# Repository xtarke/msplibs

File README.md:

# MSP430 libs: exemplos para Microcontroladores MSP430

Notas, exemplos e bibliotecas para a disciplina de Microntroladores do Instituto Ferderal de Santa Catarina

## Getting Started

Clone o repositório e adicione os arquivos no seu projeto. Evite compilar mais de uma função main.

## Circuitos

- [Hardware LCD e IRQ externo](./figuras/display_irq.png)
- [Hardware diplays de 7 segmentos e WDT](./figuras/wdt_disp.png)

## Gravação com MSPDEBUG

```bash
mspdebug -n rf2500 "prog ./Debug/msplibs.out"
```

[Launchpad Linux](https://hackaday.com/2010/08/11/how-to-launchpad-programming-with-linux/)

https://dlbeer.co.nz/mspdebug/

##  Launchpad G2553

	- Inverter os jumpers Rx e TX no kit para receber/enviar comandos pela UART e computador.

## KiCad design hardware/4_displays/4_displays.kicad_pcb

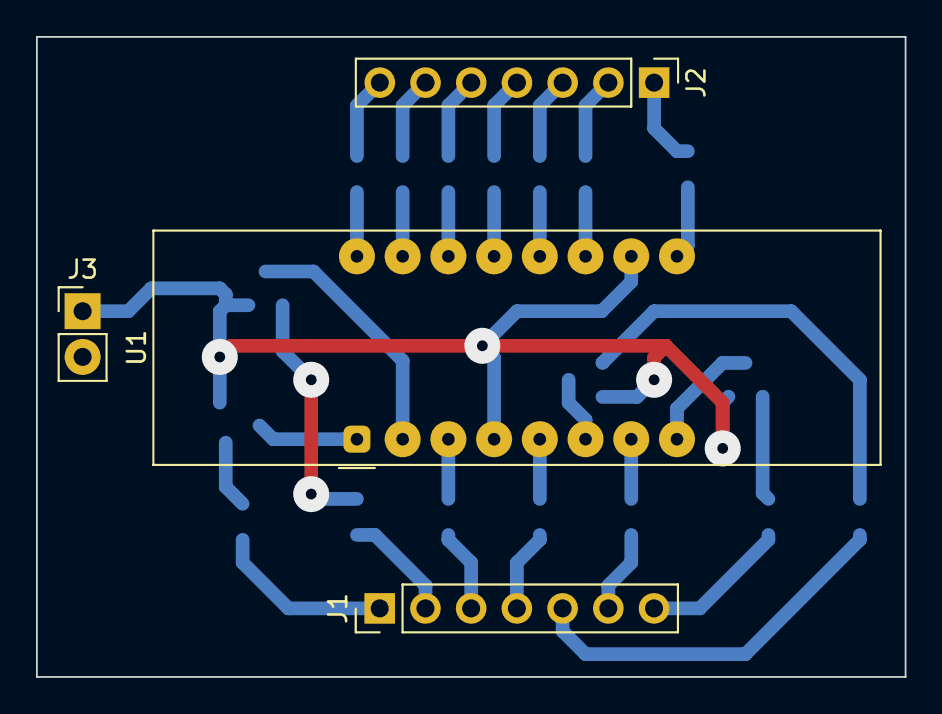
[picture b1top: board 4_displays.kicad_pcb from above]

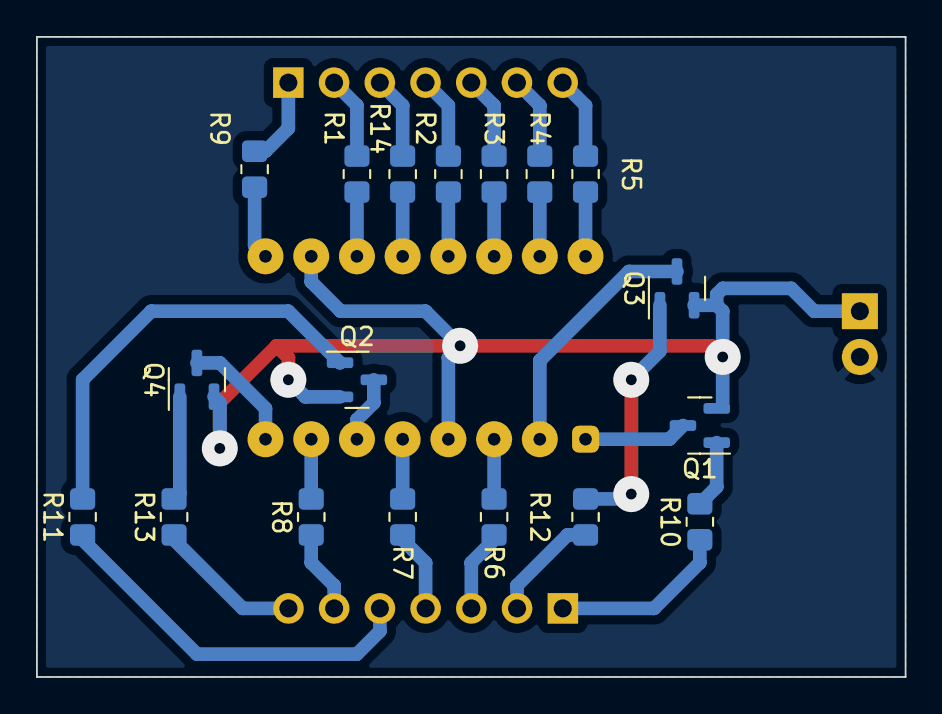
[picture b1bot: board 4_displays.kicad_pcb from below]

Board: 2 copper layers, 48.3 x 35.6 mm, 22 parts (18 on the bottom side), 33 nets.

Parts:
J1, J2: Conn_01x07_Male; PinHeader_1x07_P2.54mm_Vertical
J3: Conn_01x02_Male; PinHeader_1x02_P2.54mm_Vertical
Q1, Q2, Q3, Q4: BC807; SOT-23
R1, R2, R3, R4, R5, R6, R7, R8, R9, R14: 330; R_0805_2012Metric_Pad1.20x1.40mm_HandSolder
R10, R11, R12, R13: 2k2; R_0805_2012Metric_Pad1.20x1.40mm_HandSolder
U1: LTC-4627JG; LTC-4627Jx

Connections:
+3V3: J3.1, Q1.2 (E), Q2.2 (E), Q3.2 (E), Q4.2 (E), U1.4 (AL1-2), U1.10 (AL3)
A: R3.1, U1.14 (A)
B: R5.1, U1.16 (B)
C: R2.2, U1.13 (C)
CA1: Q1.3 (C), U1.1 (CA1)
CA2: Q3.3 (C), U1.2 (CA2)
CA3: Q2.3 (C), U1.6 (CA3)
CA4: Q4.3 (C), U1.8 (CA4)
CL1-2: R14.2, U1.12 (CL1-2)
CL3: R9.2, U1.9 (CL3)
D: R6.2, U1.3 (D)
D1: J1.1, R10.1
D2: J1.2, R12.1
D3: J1.5, R11.1
D4: J1.7, R13.1
DP: R8.2, U1.7 (DP)
E: R7.2, U1.5 (E)
F: R1.2, U1.11 (F)
G: R4.2, U1.15 (G)
unnamed: Q1.1 (B), R10.2
unnamed: Q2.1 (B), R11.2
unnamed: Q3.1 (B), R12.2
unnamed: Q4.1 (B), R13.2
unnamed: J2.2, R1.1
unnamed: J2.4, R2.1
unnamed: J2.5, R3.2
unnamed: J2.6, R4.1
unnamed: J2.7, R5.2
unnamed: J1.3, R6.1
unnamed: J1.4, R7.1
unnamed: J1.6, R8.1
unnamed: J2.1, R9.1
unnamed: J2.3, R14.1

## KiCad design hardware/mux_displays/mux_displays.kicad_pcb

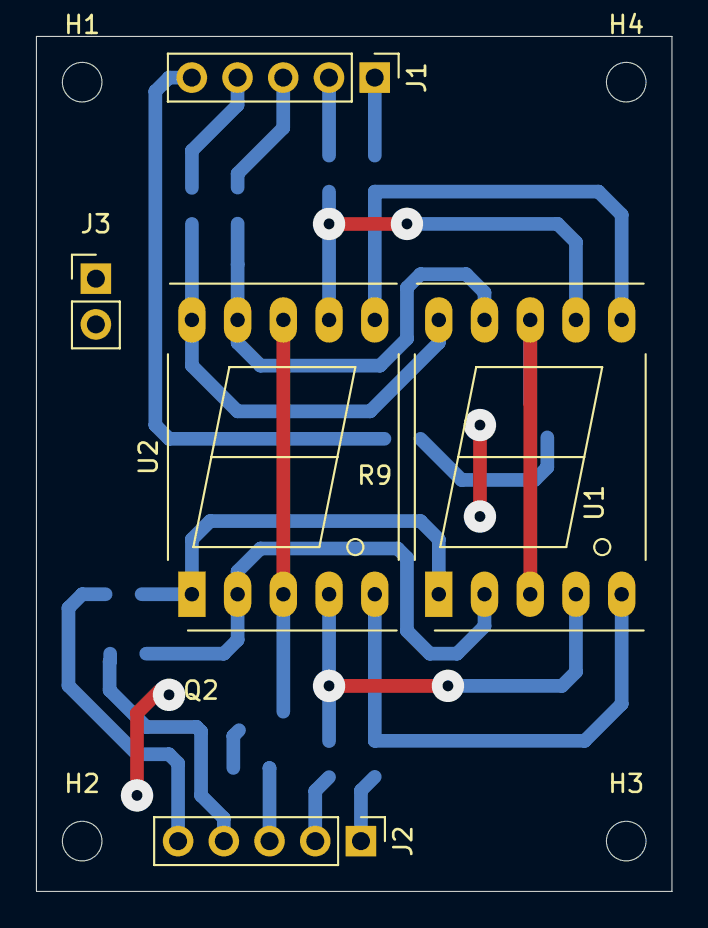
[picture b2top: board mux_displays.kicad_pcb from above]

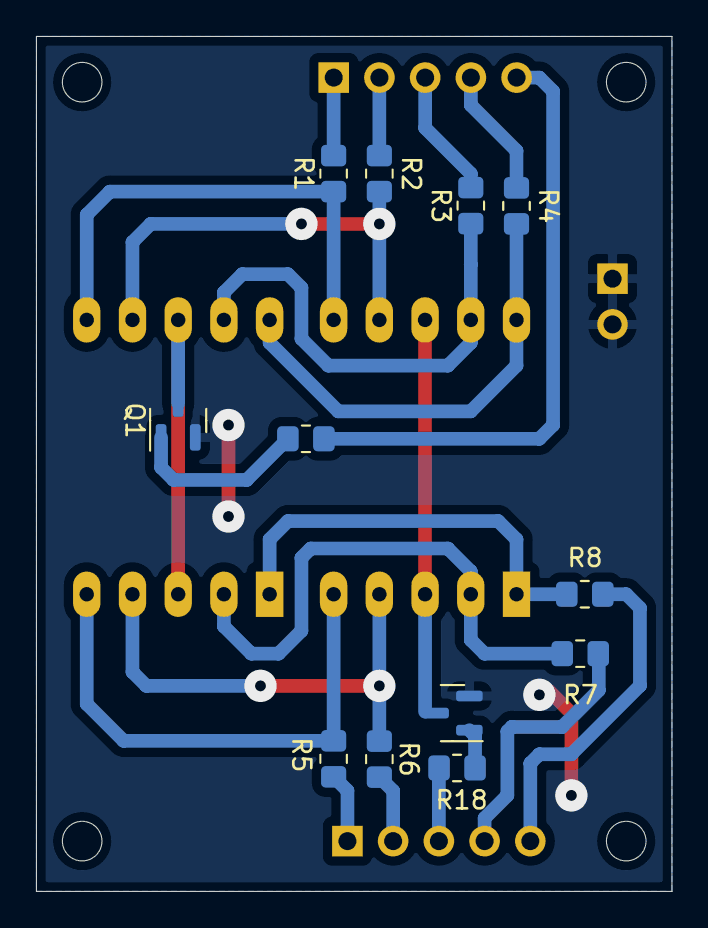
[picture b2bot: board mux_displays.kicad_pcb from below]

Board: 2 copper layers, 35.3 x 47.5 mm, 21 parts (12 on the bottom side), 23 nets.

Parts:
H1, H2, H3, H4: MountingHole; MountingHole_2.2mm_M2
J1, J2: Conn_01x05_Male; PinHeader_1x05_P2.54mm_Vertical
J3: Conn_01x02_Male; PinHeader_1x02_P2.54mm_Vertical
Q1, Q2: BC817; SOT-23
R1, R2, R3, R4, R5, R6, R7, R8: 330; R_0805_2012Metric_Pad1.20x1.40mm_HandSolder
R9, R18: 2k2; R_0805_2012Metric_Pad1.20x1.40mm_HandSolder
U1, U2: KCSC02-123; 7SegmentLED_LTS6760_LTS6780

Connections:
A: R2.1, U1.7 (A), U2.7 (A)
B: R1.1, U1.6 (B), U2.6 (B)
C: R6.1, U1.4 (C), U2.4 (C)
D: R7.1, U1.2 (D), U2.2 (D)
D1: J1.5, R9.2
D2: J2.3, R18.2
DP: R5.1, U1.5 (DP), U2.5 (DP)
E: R8.1, U1.1 (E), U2.1 (E)
F: R3.1, U1.9 (F), U2.9 (F)
G: R4.1, U1.10 (G), U2.10 (G)
GND: J3.1, J3.2, Q1.2 (E), Q2.2 (E)
unnamed: J1.1, R1.2
unnamed: J1.2, R2.2
unnamed: J1.3, R3.2
unnamed: J1.4, R4.2
unnamed: J2.1, R5.2
unnamed: J2.2, R6.2
unnamed: J2.4, R7.2
unnamed: J2.5, R8.2
unnamed: Q1.1 (B), R9.1
unnamed: Q1.3 (C), U1.3 (CC), U1.8 (CC)
unnamed: Q2.1 (B), R18.1
unnamed: Q2.3 (C), U2.3 (CC), U2.8 (CC)

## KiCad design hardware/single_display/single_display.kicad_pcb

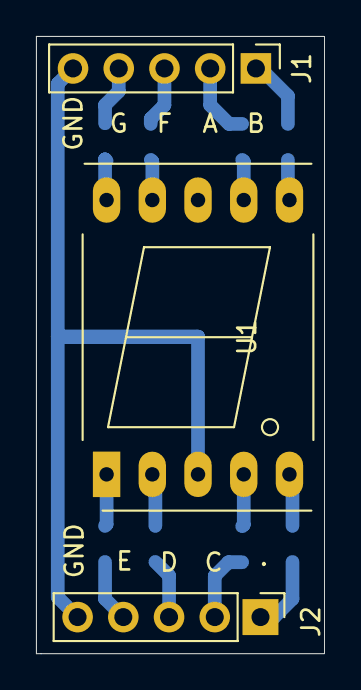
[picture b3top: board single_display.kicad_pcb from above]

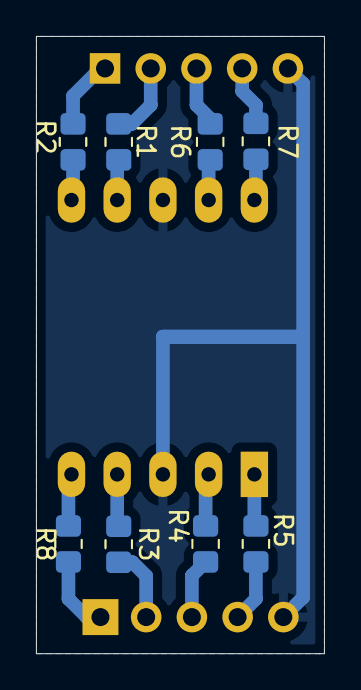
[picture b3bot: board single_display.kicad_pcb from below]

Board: 2 copper layers, 16.0 x 34.3 mm, 11 parts (8 on the bottom side), 17 nets.

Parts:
J1, J2: Conn_01x05_Male; PinHeader_1x05_P2.54mm_Vertical
R1, R2, R3, R4, R5, R6, R7, R8: 330; R_0805_2012Metric_Pad1.20x1.40mm_HandSolder
U1: KCSC02-123; 7SegmentLED_LTS6760_LTS6780

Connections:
A: J1.2, R1.2
B: J1.1, R2.2
C: J2.2, R3.2
D: J2.3, R4.2
DP: J2.1, R8.2
E: J2.4, R5.2
F: J1.3, R6.2
G: J1.4, R7.2
GND: J1.5, J2.5, U1.3, U1.8
unnamed: R1.1, U1.7
unnamed: R2.1, U1.6
unnamed: R3.1, U1.4
unnamed: R4.1, U1.2
unnamed: R5.1, U1.1
unnamed: R6.1, U1.9
unnamed: R7.1, U1.10
unnamed: R8.1, U1.5

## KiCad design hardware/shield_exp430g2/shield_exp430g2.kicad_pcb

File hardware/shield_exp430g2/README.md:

# Interface shield

This shield connects all microcontroller (MSP-EXP430G2 - MSP430G2553) pins to the car's power board. Go to [Power Board](https://github.com/xtarke/avrlibs/tree/master/shields/carrinho_potencia) for more hardware information.

See [this schematic](schematic.pdf).

## Analog pins

| Analog input  | MSP pin  | Board label  | Signal |
| ------------- | -------- | ------------ | ------ |
| A0            | P1.0     |   ADC0       | Bat0   |
| A3            | P1.3     |   ADC1       | Bat1   |
| ?             |  ?       |   ADC2       | Ampop1 |
| ?             |  ?       |   ADC3       | Ampop2 |

## Ultrasonic sensor

| MSP Pin | Signal|
| ------- | ------|
| P1.5    | Echo0 |
| P1.4    | Trig0 |
| P1.6    | Echo1 |
| P1.7    | Trig1 |

## Motors

**Caution**, P2.1 and P2.2 are connected to the same timer comparator as well as P2.4 and P2.5.

| MSP Pin    | Signal|  Board label |
| ---------- | ------| ------------ |
| P2.1/TA1.1 | PWM1  |  M1          |
| P2.2/TA1.1 | PWM1N |  M1N         |
| P2.4/TA1.2 | PWM2  |  M2          |
| P2.5/TA1.2 | PWM2N |  M2N         |

## Espeed econder

| MSP Pin | Signal |  Board label |
| ------- | ------ | ------------ |
| P2.6    | D0     | ENC0         |
| P2.7    | D1     | ENC1         |

## Optic sensor

| MSP Pin | Signal | Board label |
| ------- | ------ | ----------- |
| P2.0    | R_TCRT | R DIR       |
| P2.3    | L_TCRT | L ESQ       |

## UART

| MSP Pin | Signal |
| ------- | ------ |
| P1.2    | TX     |
| P1.3    | RX     |

## Assembly

EXP430G2 with MSP430G2553 
Shield and EXP430G2 
Power board. Connection with 26 pin flat cable

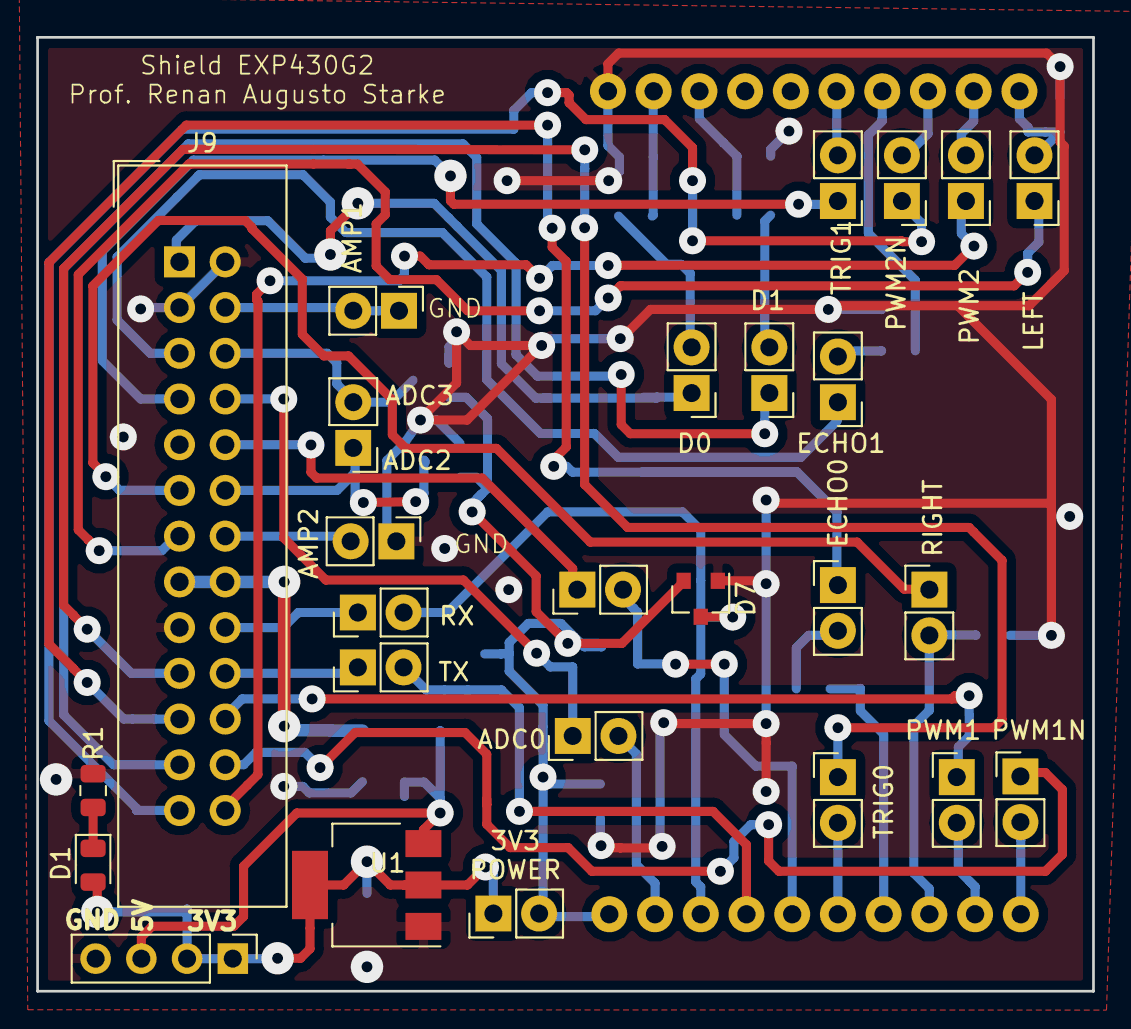
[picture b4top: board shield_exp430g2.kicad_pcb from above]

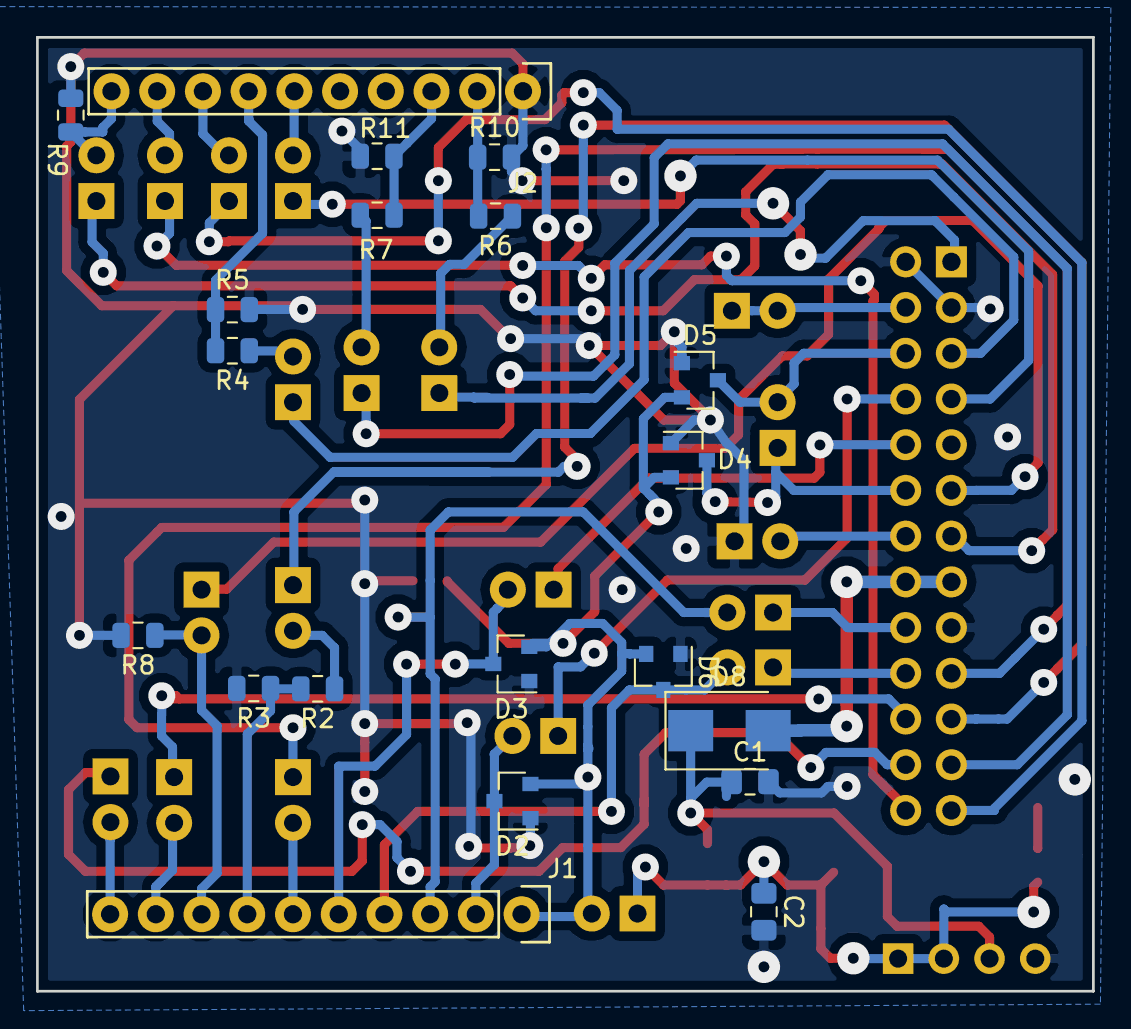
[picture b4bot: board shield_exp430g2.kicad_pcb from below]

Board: 2 copper layers, 58.7 x 53.0 mm, 46 parts (20 on the bottom side), 46 nets.

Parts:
C1, C2: 100n; C_0805_2012Metric_Pad1.15x1.40mm_HandSolder
D1: LED; LED_0805_2012Metric
D2, D3, D4, D5, D6, D7: BAT54S; SOT-23
D8: D_Schottky; D_SMB
J1, J2: Digital; Socket_Strip_Arduino_1x10
J3, J4, J5, J6, J7, J8, J10, J11, J12, J13, J15, J16, J17, J18, J19, J20, J21, J22, J23, J24: Conn_01x02_Male; PinHeader_1x02_P2.54mm_Vertical
J9: Conn_02x13_Odd_Even; IDC-Header_2x13_P2.54mm_Vertical
J14: Conn_01x04_Male; PinHeader_1x04_P2.54mm_Vertical
R1: R; R_0805_2012Metric
R2, R4, R6, R7: 10k; R_0805_2012Metric
R3, R5, R8, R9, R10, R11: 15k; R_0805_2012Metric
U1: NCP1117-3.3_SOT223; SOT-223-3_TabPin2

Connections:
+3V3: D2.2, D3.2, D4.2, D5.2, D6.2, D7.2, J1.1, J3.2
+5V: C1.1, D8.1, J14.3, U1.3
+5VP: D8.2, J9.15, J9.16
ADC0: J6.1, J9.8
ADC1: J7.1, J9.10
ADC2: D4.3, J8.1, J9.12
ADC3: D5.3, J8.2, J9.6
AMP1: J4.1, J4.2, J9.4
AMP2: J5.2, J9.14
D0: J9.1, J21.1
D1: J9.23, J24.1
Echo0: J9.21, J10.1
Echo1: J9.5, J12.1
GND: C1.2, C2.2, D2.1, D3.1, D4.1, D5.1, D6.1, D7.1, J2.1, J5.1, J9.2, J9.3, J9.17, J14.4, R1.2, R3.2, R5.2, R8.2, R9.2, R10.2, R11.2, U1.1
L_TCRT: J9.13, J20.1
unnamed: C2.1, D1.2, J3.1, J14.1, J14.2, U1.2
unnamed: D1.1, R1.1
unnamed: J10.2, R2.1
unnamed: J12.2, R4.1
unnamed: J21.2, R6.1
unnamed: J24.2, R7.1
P1.0: D2.3, J1.2, J6.2
P1.1: D7.3, J1.3, J23.2
P1.2: D6.3, J1.4, J22.2
P1.3: D3.3, J1.5, J7.2
P1.4: J1.6, J11.2
P1.5: J1.7, R2.2, R3.1
P1.6: J2.7, R4.2, R5.1
P1.7: J2.6, J13.2
P2.0: J1.8, J19.2, R8.1
P2.1: J1.9, J15.2
P2.2: J1.10, J16.2
P2.3: J2.10, J20.2, R9.1
P2.4: J2.9, J17.2
P2.5: J2.8, J18.2
P2.6: J2.2, R6.2, R10.1
P2.7: J2.3, R7.2, R11.1
PWM1: J9.22, J15.1
PWM1N: J9.24, J16.1
PWM2: J9.26, J17.1
PWM2N: J9.25, J18.1
RXB: J9.20, J22.1
R_TCRT: J9.11, J19.1
TXB: J9.18, J23.1
Trig0: J9.19, J11.1
Trig1: J9.7, J13.1

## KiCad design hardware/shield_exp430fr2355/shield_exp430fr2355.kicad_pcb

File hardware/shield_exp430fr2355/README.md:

# Interface shield

This shield connects microcontroller (MSP-EXP430FR2355) pins to the car's power board. Go to [Power Board](https://github.com/xtarke/avrlibs/tree/master/shields/carrinho_potencia) for more hardware information.

See [this schematic](schematic.pdf).

## Analog pins

| Analog input  | MSP pin  | Board label  | Signal |
| ------------- | -------- | ------------ | ------ |
| A1            | P1.1     |   ADC0       | Bat0   |
| A2            | P1.2     |   ADC1       | Bat1   |
| ?             |  ?       |   ADC2       | Ampop1 |
| ?             |  ?       |   ADC3       | Ampop2 |

## Ultrasonic sensor

| MSP Pin | Signal|
| ----------- | ------|
| P2.0/TB1.1  | Echo0 |
| P2.2        | Trig0 |
| P2.1/TB1.2  | Echo1 |
| P2.4        | Trig1 |

## Motors

| MSP Pin    | Signal|  Board label |
| ---------- | ------| ------------ |
| P6.0/TB3.1 | PWM1  |  M1          |
| P6.1/TB3.2 | PWM1N |  M1N         |
| P6.2/TB3.3 | PWM2  |  M2          |
| P6.3/TB3.4 | PWM2N |  M2N         |

## Espeed econder

| MSP Pin | Signal |  Board label |
| ------- | ------ | ------------ |
| P5.0    | D0     | ENC0         |
| P5.1    | D1     | ENC1         |

## Optic sensor

| MSP Pin | Signal | Board label |
| ------- | ------ | ----------- |
| P5.4    | R_TCRT | R DIR       |
| P3.0    | L_TCRT | L ESQ       |

## UART

| MSP Pin | Signal |
| ------- | ------ |
| P1.7    | TX     |
| P1.6    | RX     |

## Assembly

Shield and EXP430FR2355 

Shield, EXP430FR2355 and chassi. 

Power board. Connection with 26 pin flat cable

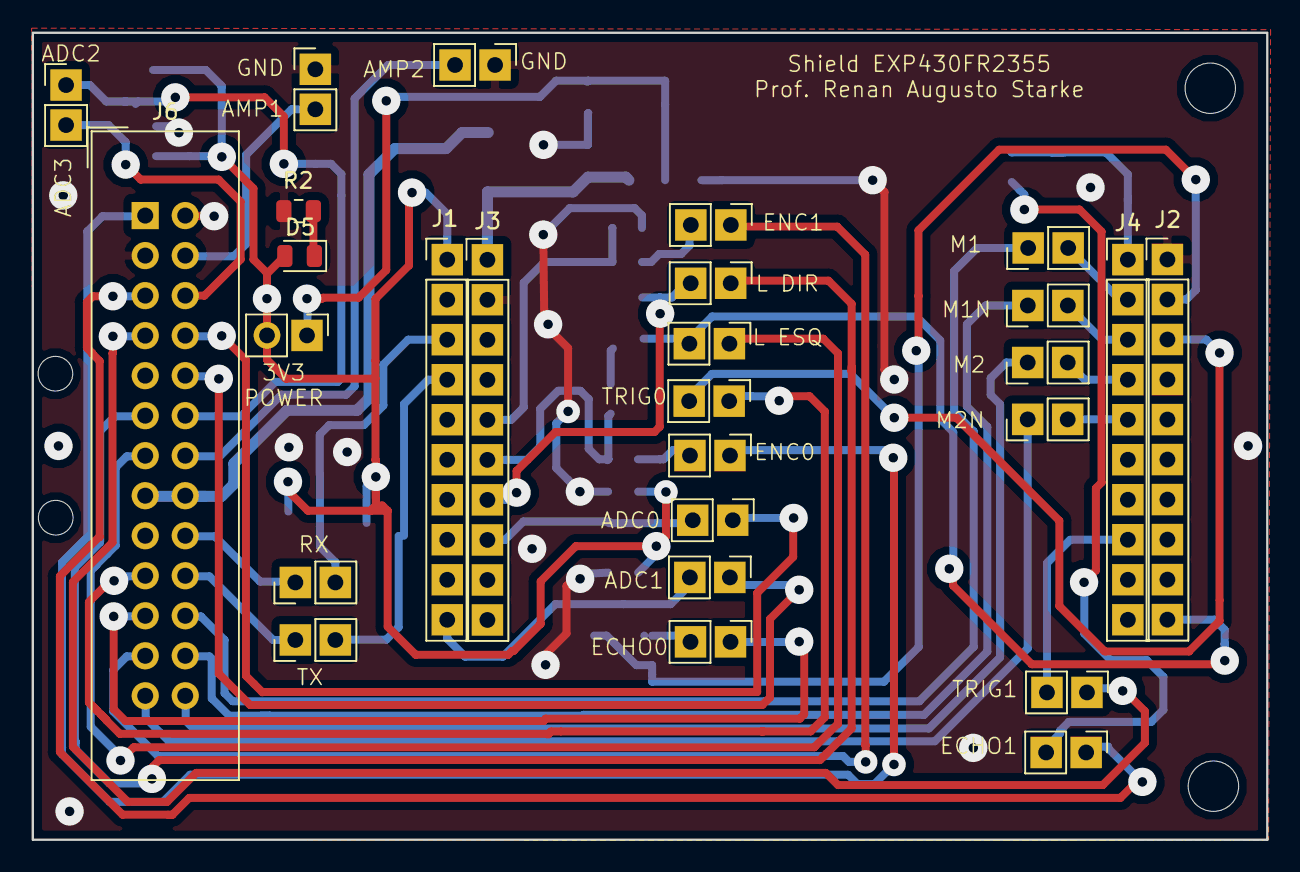
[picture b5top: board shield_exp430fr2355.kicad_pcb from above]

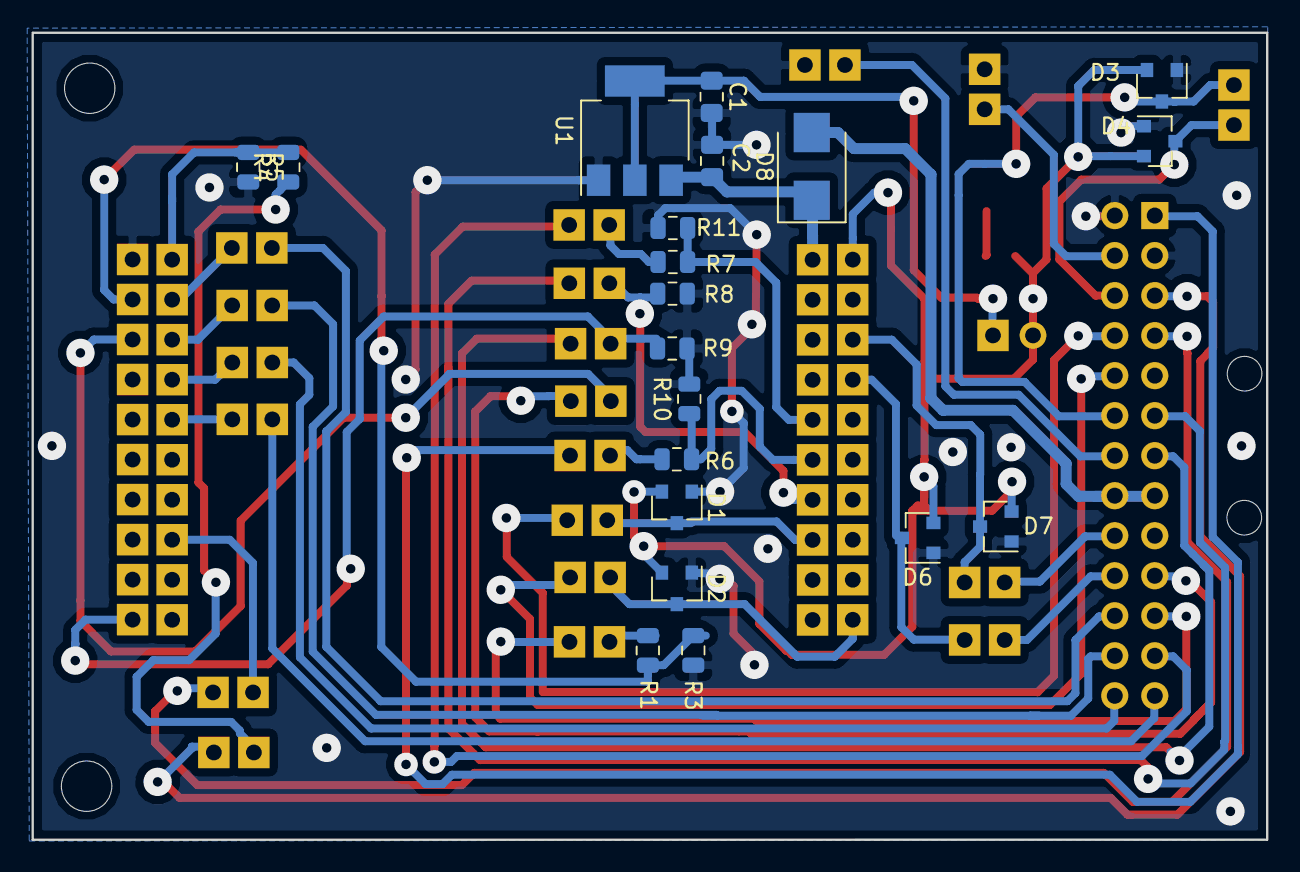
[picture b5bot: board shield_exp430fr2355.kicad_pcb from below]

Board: 2 copper layers, 78.4 x 51.2 mm, 51 parts (20 on the bottom side), 46 nets.

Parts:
C1, C2: 100n; C_0805_2012Metric_Pad1.15x1.40mm_HandSolder
D1, D2, D3, D4, D6, D7: BAT54S; SOT-23
D5: LED; LED_0805_2012Metric
D8: D_Schottky; D_SMB
H1, H2: MountingHole; MountingHole_2.2mm_M2
H3, H4: MountingHole; MountingHole_3.2mm_M3
J1: TI_BOOSTER_40_J1; PinHeader_1x10_P2.54mm_Vertical
J2: TI_BOOSTER_40_J2; PinHeader_1x10_P2.54mm_Vertical
J3: TI_BOOSTER_40_J3; PinHeader_1x10_P2.54mm_Vertical
J4: TI_BOOSTER_40_J4; PinHeader_1x10_P2.54mm_Vertical
J6: Conn_02x13_Odd_Even; IDC-Header_2x13_P2.54mm_Vertical
J7, J8, J9, J10, J12, J13, J14, J15, J16, J17, J18, J19, J20, J21, J22, J23, J24, J25, J27, J28: Conn_01x02_Male; PinHeader_1x02_P2.54mm_Vertical
R1, R4, R6, R7: 10k; R_0805_2012Metric
R2: 820R; R_0805_2012Metric
R3, R5, R10, R11: 15k; R_0805_2012Metric
R8, R9: 15K; R_0805_2012Metric
U1: NCP1117-3.3_SOT223; SOT-223-3_TabPin2

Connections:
+3V3: D1.2, D2.2, D3.2, D4.2, D5.2, D6.2, D7.2, J1.1, J7.2
+5V: C2.1, D8.1, J3.1, U1.3
+5VP: D8.2, J6.15, J6.16
ADC0: J6.8, J12.1
ADC1: J6.10, J21.1
ADC2: D3.3, J6.12, J8.1
ADC3: D4.3, J6.6, J8.2
AMP1: J6.4, J9.2
AMP2: J6.14, J10.2
D0: J6.1, J22.1
D1: J6.23, J23.1
Echo0: J6.21, J13.1
Echo1: J6.5, J19.1
GND: C1.2, C2.2, D1.1, D2.1, D3.1, D4.1, D6.1, D7.1, J2.1, J3.2, J6.2, J6.3, J9.1, J10.1, R2.2, R3.2, R5.2, R8.2, R9.2, R10.2, R11.2, U1.1
L_TCRT: J6.13, J25.1
unnamed: C1.1, J7.1, U1.2
unnamed: D5.1, R2.1
unnamed: J13.2, R1.1
unnamed: J19.2, R4.1
unnamed: J22.2, R6.1
unnamed: J23.2, R7.1
P1.1: D1.3, J3.8, J12.2
P1.2: D2.3, J1.10, J21.2
P1.6: D7.3, J1.3, J28.2
P1.7: D6.3, J1.4, J27.2
P2.0: J2.2, R1.2, R3.1
P2.1: J4.1, R4.2, R5.1
P2.2: J2.3, J14.2
P2.4: J4.8, J20.2
P3.0: J2.10, J25.2, R9.1
P5.0: J3.6, R6.2, R10.1
P5.1: J3.5, R7.2, R11.1
P5.4: J3.7, J24.2, R8.1
P6.0: J4.2, J15.2
P6.1: J4.3, J16.2
P6.2: J4.4, J17.2
P6.3: J4.5, J18.2
PWM1: J6.22, J15.1
PWM1N: J6.24, J16.1
PWM2: J6.26, J17.1
PWM2N: J6.25, J18.1
RXB: J6.20, J27.1
R_TCRT: J6.11, J24.1
TXB: J6.18, J28.1
Trig0: J6.19, J14.1
Trig1: J6.7, J20.1

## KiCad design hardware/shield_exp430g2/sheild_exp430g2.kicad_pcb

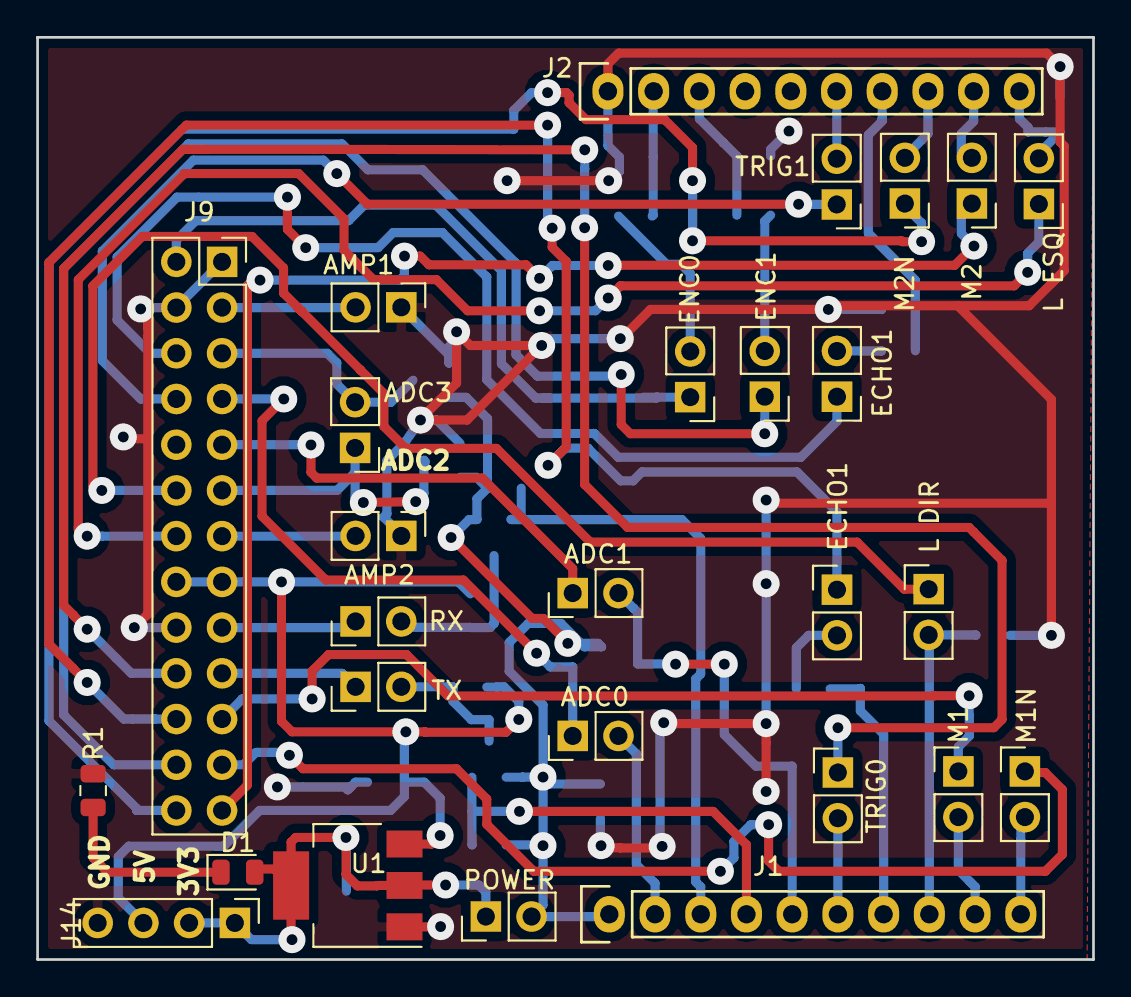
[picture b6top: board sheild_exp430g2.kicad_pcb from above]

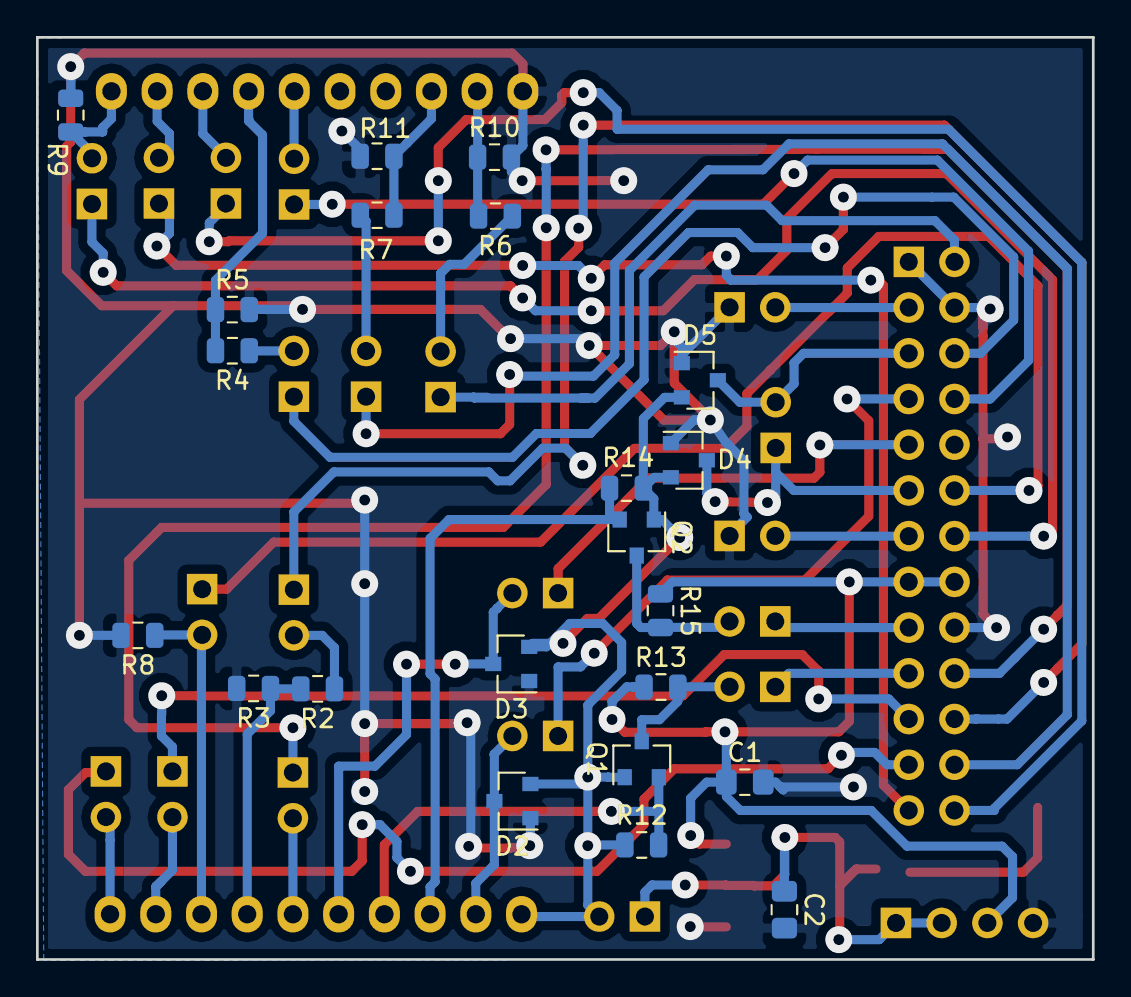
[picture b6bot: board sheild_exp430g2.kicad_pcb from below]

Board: 2 copper layers, 58.7 x 51.2 mm, 49 parts (22 on the bottom side), 47 nets.

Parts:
ADC0, ADC1, ADC3: Conn_01x02_Male; PinHeader_1x02_P2.54mm_Vertical
AMP1, AMP2: Conn_01x02_Male; PinHeader_1x02_P2.54mm_Vertical
C1, C2: 100n; C_0805_2012Metric_Pad1.15x1.40mm_HandSolder
D1: LED; LED_0805_2012Metric
D2, D3, D4, D5: BAT54S; SOT-23
ECHO1, ECHO1#2: Conn_01x02_Male; PinHeader_1x02_P2.54mm_Vertical
ENC0, ENC1: Conn_01x02_Male; PinHeader_1x02_P2.54mm_Vertical
J1, J2: Digital; Socket_Strip_Arduino_1x10
J9: Conn_02x13_Odd_Even; PinSocket_2x13_P2.54mm_Vertical
J14: Conn_01x04_Male; PinHeader_1x04_P2.54mm_Vertical
L DIR: Conn_01x02_Male; PinHeader_1x02_P2.54mm_Vertical
L ESQ: Conn_01x02_Male; PinHeader_1x02_P2.54mm_Vertical
M1, M1N, M2, M2N: Conn_01x02_Male; PinHeader_1x02_P2.54mm_Vertical
POWER: Conn_01x02_Male; PinHeader_1x02_P2.54mm_Vertical
Q1, Q2: 2N7002; SOT-23
R1: R; R_0805_2012Metric
R2, R4, R6, R7: 10k; R_0805_2012Metric
R3, R5, R8, R9, R10, R11: 20K; R_0805_2012Metric
R12, R13, R14, R15: 2k2; R_0805_2012Metric
RX: Conn_01x02_Male; PinHeader_1x02_P2.54mm_Vertical
TRIG0, TRIG1: Conn_01x02_Male; PinHeader_1x02_P2.54mm_Vertical
TX: Conn_01x02_Male; PinHeader_1x02_P2.54mm_Vertical
U1: NCP1117-3.3_SOT223; SOT-223-3_TabPin2

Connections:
+3V3: D2.2, D3.2, D4.2, D5.2, J1.1, POWER.2, Q1.1, Q2.1, R12.1, R14.1
+5V: C1.1, J9.15, J9.16, J14.3, R13.1, R15.1, U1.3
ADC0: ADC0.1, J9.7
ADC1: ADC1.1, J9.9
ADC2: ADC3.1, D4.3, J9.11
ADC3: ADC3.2, D5.3, J9.5
AMP1: AMP1.2, J9.3
AMP2: AMP2.2, J9.13
D0: ENC0.1, J9.2
D1: ENC1.1, J9.24
Echo0: ECHO1#2.1, J9.22
Echo1: ECHO1.1, J9.6
GND: AMP1.1, AMP2.1, C1.2, C2.2, D2.1, D3.1, D4.1, D5.1, J2.1, J9.1, J9.4, J9.18, J14.4, R1.2, R3.2, R5.2, R8.2, R9.2, R10.2, R11.2, U1.1
L_TCRT: J9.14, L ESQ.1
unnamed: C2.1, D1.2, J14.1, J14.2, POWER.1, U1.2
unnamed: D1.1, R1.1
unnamed: ECHO1#2.2, R2.1
unnamed: ECHO1.2, R4.1
unnamed: ENC0.2, R6.1
unnamed: ENC1.2, R7.1
P1.0: ADC0.2, D2.3, J1.2
P1.1: J1.3, Q2.2, R14.2
P1.2: J1.4, Q1.2, R12.2
P1.3: ADC1.2, D3.3, J1.5
P1.4: J1.6, TRIG0.2
P1.5: J1.7, R2.2, R3.1
P1.6: J2.7, R4.2, R5.1
P1.7: J2.6, TRIG1.2
P2.0: J1.8, L DIR.2, R8.1
P2.1: J1.9, M1.2
P2.2: J1.10, M1N.2
P2.3: J2.10, L ESQ.2, R9.1
P2.4: J2.9, M2.2
P2.5: J2.8, M2N.2
P2.6: J2.2, R6.2, R10.1
P2.7: J2.3, R7.2, R11.1
PWM1: J9.21, M1.1
PWM1N: J9.23, M1N.1
PWM2: J9.25, M2.1
PWM2N: J9.26, M2N.1
RXB: J9.19, TX.1
R_TCRT: J9.12, L DIR.1
Rx: Q2.3, R15.2, RX.2
TXB: J9.17, RX.1
Trig0: J9.20, TRIG0.1
Trig1: J9.8, TRIG1.1
Tx: Q1.3, R13.2, TX.2

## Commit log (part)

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2020-02-07 Added README
2020-02-07 Added GPIO example
2020-02-27 Added display examaple
2020-02-27 Added mux displays
2020-02-28 Added lcd.c/.h
2020-03-02 Ported and tested lcd module with FR2355
2020-03-12 Added external IRQ
2020-03-16 Added macro for FR2355's GPIO activation
2020-03-20 Added figure and a example with lcd and irq
2020-03-23 Added clock system examples
2020-03-28 Added watchdog timer examples
2020-03-29 Added figures
2020-03-29 Added figures, png
2020-04-03 Addes timer A examples
2020-04-04 Added deboucers
2020-04-05 Added other comparators in Timer A example.
2020-04-23 Added timer capture example
2020-04-25 Adde PWM example
2020-04-28 Added phase-correct PWM example
2020-05-13 Added FSM application example.
2020-05-15 Corrected fsm example.
2020-05-15 Added Analog comparator examples.
2020-05-15 Adicionado exemplo do ADC10 para MSP430G2553.
2020-05-18 Ajusted analog compartor example.
2020-05-18 Added ADC trigger by timer.
2020-05-19 Added DTC ADC examples
2020-05-20 Added ADC, DTC and timer example.
2020-05-20 Corrected ADC trigger.
2020-05-21 Add PGA with ADC.
2020-05-23 Added SAC example.
2020-05-25 Adjusting SAC example.
2020-05-25 Hardware Uart. First testst.
2020-05-25 Hardware UART. Added main.
2020-05-26 Added UART example (MSP430G2553)
2020-05-28 Added and validated I2C library.
2020-05-29 Adde SPI library and example.
2020-06-01 Added SPI aplication: DS3234 RTC Changed UCSA to UCSB in SPI library.
2020-06-04 Added FR2355 uart library. Corrected uart header in G5553.
2020-06-08 Added FR2355 I2C Library.
2020-06-10 Added EXP430G2 shield
2020-06-12 Added schematic pins
2020-06-19 Finish PCB layout
2020-06-22 Increased GND copper
2020-06-22 Otimized some tracks
2020-06-22 Renamed project
2020-06-22 Added fr2355 shield
2020-06-23 Finished schematic
2020-06-24 Routing tracks
2020-06-24 FR2355 interface board finished
2020-06-25 Added board documentation
2020-06-25 Added schematic pdf
2020-06-25 Rotated schematic
2020-06-25 Added documentation files
2020-06-26 Added 3d Models
2020-06-27 Added 3d models, corrected PCB dimensions
2020-06-27 Corrected readme
2020-07-02 Added plano
2020-08-20 Added 4 pwm outputs example.
2020-09-01 Updated README and corrected some codes
2020-09-04 Added a list of Proteus problens.
2020-09-10 Added I2C information regarding Proteus simulation.
2020-09-17 - Revised README, added timer capture example.
2020-09-18 Added some info in source code.
2020-09-21 Updated shield hardware, added uart protection!
2020-09-29 Corrected UART bug.
2020-10-01 Added ADC10/F2132 Example. Runs in Proteus.
2020-10-02 Adicionado exemplo do ADC com trigger por timer.
2020-10-05 Added lmp for UART in G2553
2020-10-05 Added aligment info
2020-10-05 Added aligment holes
2020-10-19 Updated FR2553 PCB. Vias are now 1.8mm
2020-10-19 Updated FR2553 PCB. Connector pads are now 2x2mm
2020-10-20 Updated g2553 board
2020-10-22 Added diode
2020-11-06 Added CC110L Air module example for Launchpad EXPG2553
2020-12-11 Corrected some issues.
2020-12-15 Change 26 via connector
2020-12-21 Fix delays. Use of stdint.h.
2021-02-09 Added FR2355 WDT example
2021-02-19 Update 05_main_simple_wd_timer_fr2355.c
    Unlock GPIO from high impedance mode.
2021-03-09 Added board info
2021-05-28 Some corrections
2021-05-28 Added hex codecomposer tutorial
2021-05-28 Added proteus screenshot
2021-08-09 Corrected text
2022-05-02 Added single display board
2022-05-03 Projeto em kicad 6
2022-05-25 Adicionado exemplo timer B. Adicionado comentários para DCO FR2355
2022-05-25 Adicionado furos na placa de displays
2022-05-31 Added pdf for mux displays
2022-06-03 Criado o projeto de 4 displays
2022-06-24 Adicionado comentário sobre a temporização do debouncer por contagem.
2022-07-05 Corrigido registrador no modo captura.
2022-07-05 Pull
2022-07-12 Adicionado baudrate de 9600
2022-08-18 Correção do esquemático
2022-11-07 Adicionado exemplo de FSM
2022-11-08 Corrigido comentários do exemplo do debouncer por contagem
2025-04-28 Corrigido header dos displays mux
2025-06-06 Added pmctl to timer example
2025-06-07 Added timer B pwm sample
2025-06-07 Added docs
2025-07-19 Updated sample
2025-07-26 Retirado tutor
2025-07-28 Added OLED sample and docs
2025-07-28 Resized figure
2025-07-28 Added oled init delay
2025-08-22 Atualizado REAME
2025-08-29 Adicionado exemplo blink asm
2025-11-21 Adicionado mais exemplos de UART e I2C.
